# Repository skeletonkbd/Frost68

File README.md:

# Frost68

アクリル積層ケースを使った Alice 配列のキーボードです。（開発時名称: Skeleton68rev2）

Firmware: https://github.com/skeletonkbd/qmk_firmware/tree/Frost68/keyboards/skeletonkbd/frost68

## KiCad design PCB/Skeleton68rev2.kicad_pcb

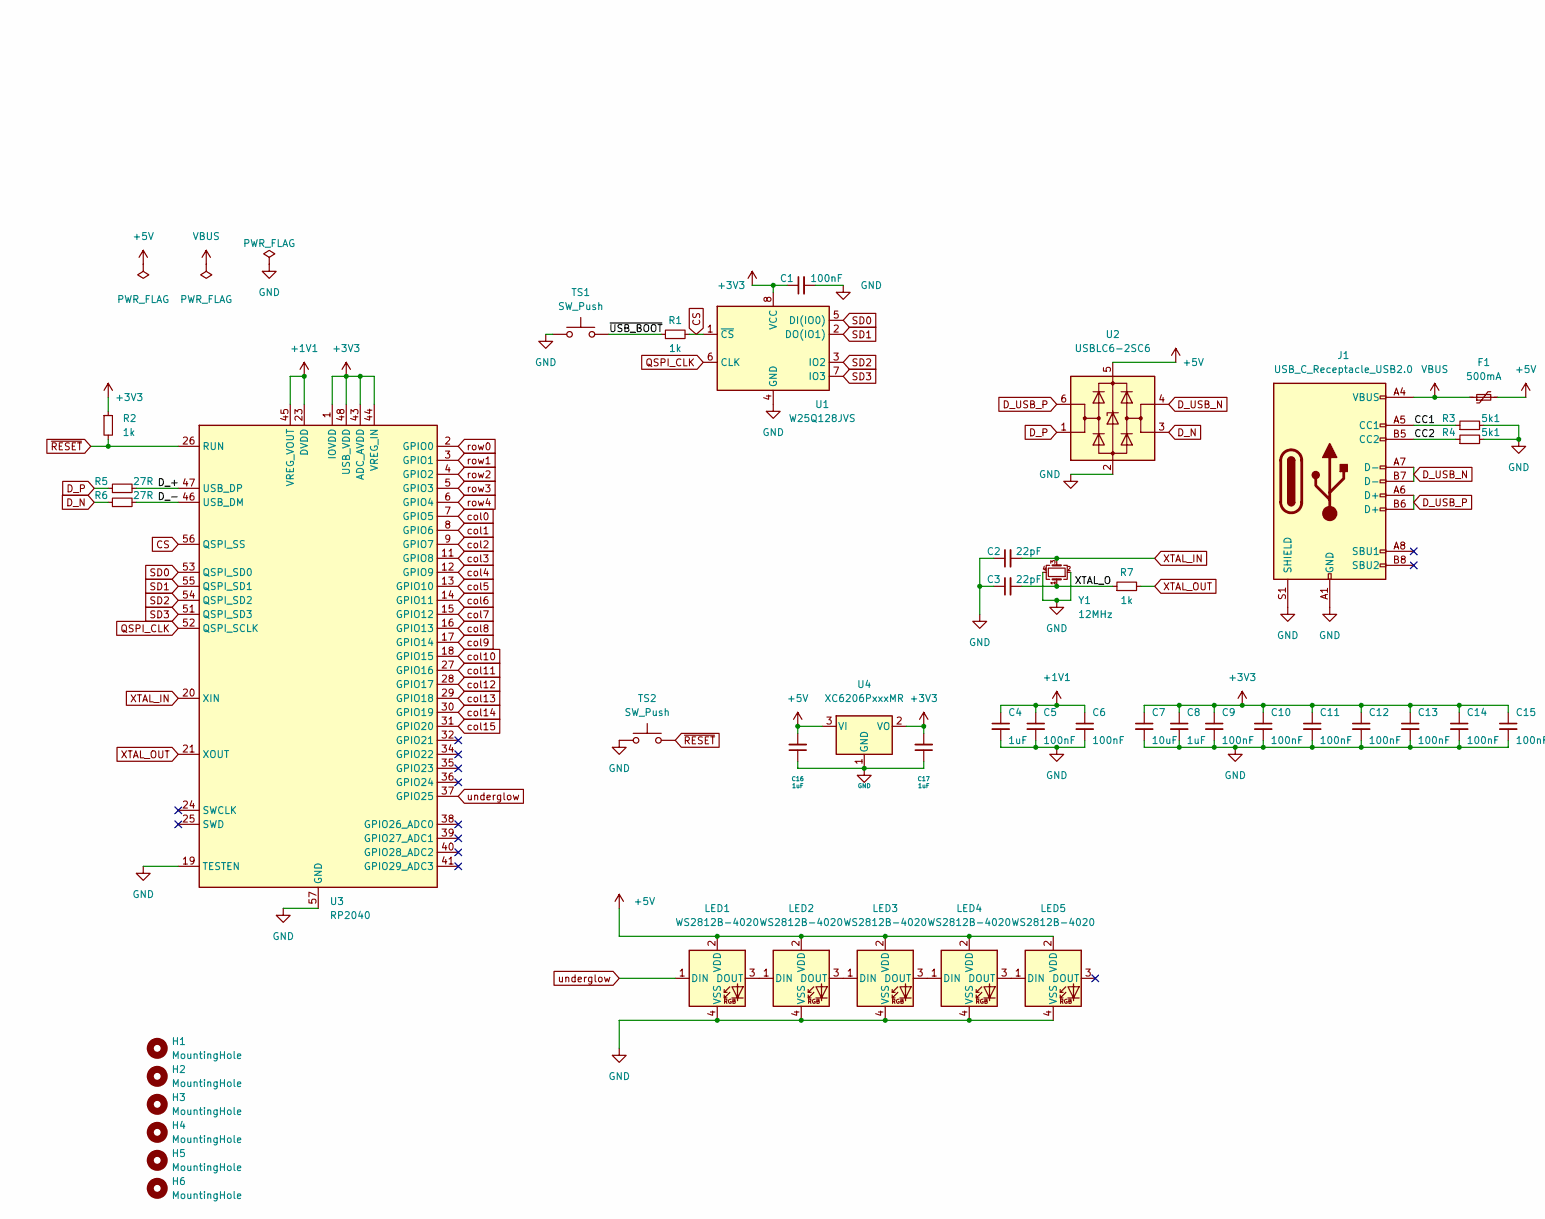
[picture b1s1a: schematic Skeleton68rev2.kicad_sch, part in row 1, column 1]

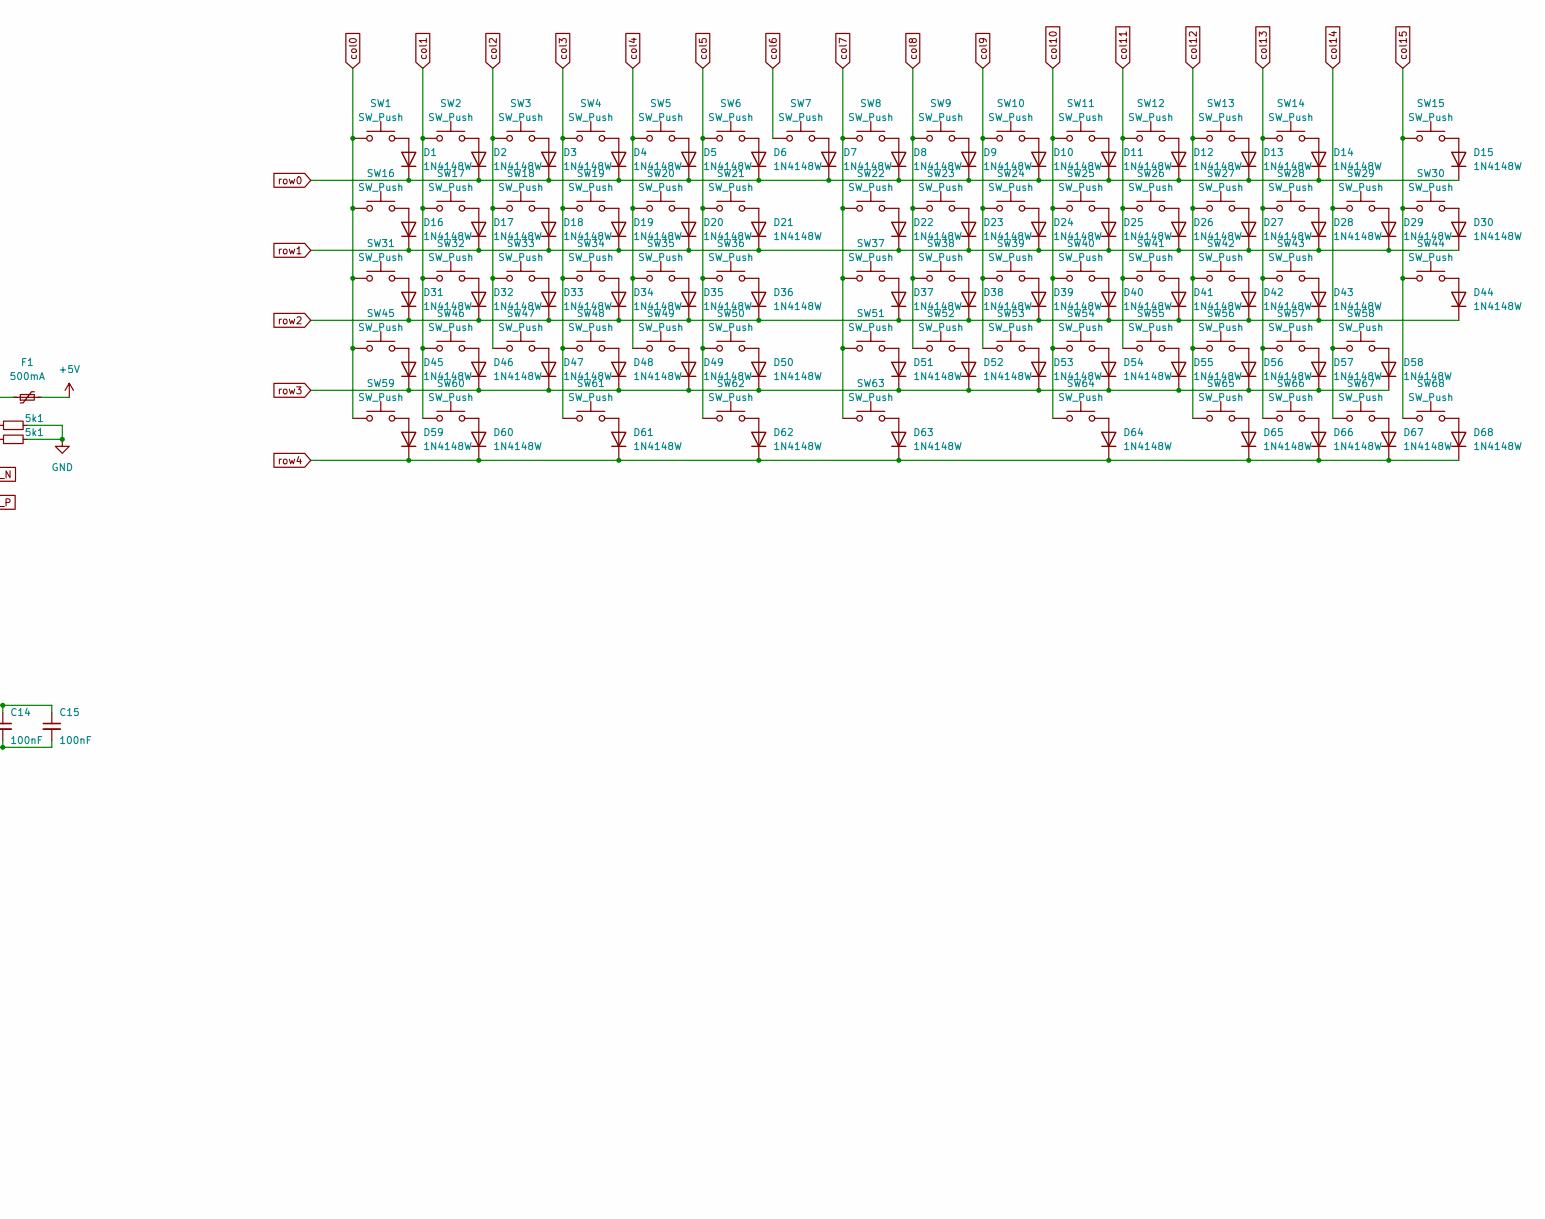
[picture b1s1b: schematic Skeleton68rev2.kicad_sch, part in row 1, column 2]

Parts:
C1, C5, C6, C9, C10, C11, C12, C13, C14, C15: 100nF; C_0402_1005Metric; MPN CL05B104KO5NNNC; LCSC C1525
C2, C3: 22pF; C_0402_1005Metric; MPN 0402CG220J500NT; LCSC C1555
C4, C8, C16, C17: 1uF; C_0402_1005Metric; MPN CL05A105KA5NQNC; LCSC C52923
C7: 10uF; C_0402_1005Metric; MPN CL05A106MQ5NUNC; LCSC C15525
D1, D2, D3, D4, D5, D6, D7, D8, D9, D10, D11, D12, D13, D14, D15, D16, D17, D18, D19, D20, D21, D22, D23, D24, D25, D26, D27, D28, D29, D30, D31, D32, D33, D34, D35, D36, D37, D38, D39, D40, D41, D42, D43, D44, D45, D46, D47, D48, D49, D50, D51, D52, D53, D54, D55, D56, D57, D58, D59, D60, D61, D62, D63, D64, D65, D66, D67, D68: 1N4148W; D_SOD-123
F1: 500mA; Fuse_1206_3216Metric; MPN nSMD050-24V; LCSC C70076
H1, H2, H3, H4, H5, H6: MountingHole; MountingHole_2.2mm_M2
J1: USB_C_Receptacle_USB2.0; USB_C_Receptacle_HRO_TYPE-C-31-M-12; MPN TYPE-C-31-M-12; LCSC C165948
LED1, LED2, LED3, LED4, LED5: WS2812B-4020
R1, R2, R7: 1k; R_0402_1005Metric; MPN 0402WGF1001TCE; LCSC C11702
R3, R4: 5k1; R_0402_1005Metric; MPN 0402WGF5101TCE; LCSC C25905
R5, R6: 27R; R_0603_1608Metric; MPN 0603WAF270JT5E; LCSC C25190
SW1, SW2, SW3, SW4, SW5, SW6, SW7, SW8, SW9, SW10, SW11, SW12, SW13, SW14, SW15, SW16, SW17, SW18, SW19, SW20, SW21, SW22, SW23, SW24, SW25, SW26, SW27, SW28, SW29, SW30, SW31, SW32, SW33, SW34, SW35, SW36, SW37, SW38, SW39, SW40, SW41, SW42, SW43, SW44, SW45, SW46, SW47, SW48, SW49, SW50, SW51, SW52, SW53, SW54, SW55, SW56, SW57, SW58, SW59, SW60, SW61, SW62, SW63, SW64, SW65, SW66, SW67, SW68: SW_Push; MX-Hotswap-1U
TS1, TS2: SW_Push; SW_SPST_SKQG_WithStem; MPN SKQGABE010; LCSC C318884
U1: W25Q128JVS; SOIC-8_5.23x5.23mm_P1.27mm; MPN W25Q16JVSSIQ; LCSC C131025
U2: USBLC6-2SC6; SOT-23-6; MPN USBLC6-2SC6; LCSC C2827654
U3: RP2040; QFN-56-1EP_7x7mm_P0.4mm_EP3.2x3.2mm
U4: XC6206PxxxMR; SOT-23; MPN XC6206P332MR; LCSC C5446
Y1: 12MHz; Crystal_SMD_3225-4Pin_3.2x2.5mm; MPN X322512MSB4SI; LCSC C9002

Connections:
+1V1: C4.1, C5.1, C6.1, U3.23 (DVDD), U3.45 (VREG_VOUT), U3.50 (DVDD)
+3V3: C1.1, C7.1, C8.1, C9.1, C10.1, C11.1, C12.1, C13.1, C14.1, C15.1, C17.2, R2.1, U1.8 (VCC), U3.1 (IOVDD), U3.10 (IOVDD), U3.22 (IOVDD), U3.33 (IOVDD), U3.42 (IOVDD), U3.43 (ADC_AVDD), U3.44 (VREG_IN), U3.48 (USB_VDD), U3.49 (IOVDD), U4.2 (VO)
+5V: C16.2, F1.2, LED1.2 (VDD), LED2.2 (VDD), LED3.2 (VDD), LED4.2 (VDD), LED5.2 (VDD), U2.5 (VBUS), U4.3 (VI)
/CC1: J1.A5 (CC1), R3.1
/CC2: J1.B5 (CC2), R4.1
/D_+: R5.2, U3.47 (USB_DP)
/D_-: R6.2, U3.46 (USB_DM)
/XTAL_O: C3.2, R7.1, Y1.1
/~USB_BOOT: R1.1, TS1.2
CS: R1.2, U1.1 (~CS), U3.56 (QSPI_SS)
D_N: R6.1, U2.3 (I/O2)
D_P: R5.1, U2.1 (I/O1)
D_USB_N: J1.A7 (D-), J1.B7 (D-), U2.4 (I/O2)
D_USB_P: J1.A6 (D+), J1.B6 (D+), U2.6 (I/O1)
GND: C1.2, C2.1, C3.1, C4.2, C5.2, C6.2, C7.2, C8.2, C9.2, C10.2, C11.2, C12.2, C13.2, C14.2, C15.2, C16.1, C17.1, J1.A1 (GND), J1.A12 (GND), J1.B1 (GND), J1.B12 (GND), J1.S1 (SHIELD), LED1.4 (VSS), LED2.4 (VSS), LED3.4 (VSS), LED4.4 (VSS), LED5.4 (VSS), R3.2, R4.2, TS1.1, TS2.1, U1.4 (GND), U2.2 (GND), U3.19 (TESTEN), U3.57 (GND), U4.1 (GND), Y1.2, Y1.4
unnamed: D1.2 (A), SW1.2
unnamed: D2.2 (A), SW2.2
unnamed: D3.2 (A), SW3.2
unnamed: D4.2 (A), SW4.2
unnamed: D5.2 (A), SW5.2
unnamed: D6.2 (A), SW6.2
unnamed: D7.2 (A), SW7.2
unnamed: D8.2 (A), SW8.2
unnamed: D9.2 (A), SW9.2
unnamed: D10.2 (A), SW10.2
unnamed: D11.2 (A), SW11.2
unnamed: D12.2 (A), SW12.2
unnamed: D13.2 (A), SW13.2
unnamed: D14.2 (A), SW14.2
unnamed: D15.2 (A), SW15.2
unnamed: D16.2 (A), SW16.2
unnamed: D17.2 (A), SW17.2
unnamed: D18.2 (A), SW18.2
unnamed: D19.2 (A), SW19.2
unnamed: D20.2 (A), SW20.2
unnamed: D21.2 (A), SW21.2
unnamed: D22.2 (A), SW22.2
unnamed: D23.2 (A), SW23.2
unnamed: D24.2 (A), SW24.2
unnamed: D25.2 (A), SW25.2
unnamed: D26.2 (A), SW26.2
unnamed: D27.2 (A), SW27.2
unnamed: D28.2 (A), SW28.2
unnamed: D29.2 (A), SW29.2
unnamed: D30.2 (A), SW30.2
unnamed: D31.2 (A), SW31.2
unnamed: D32.2 (A), SW32.2
unnamed: D33.2 (A), SW33.2
unnamed: D34.2 (A), SW34.2
unnamed: D35.2 (A), SW35.2
unnamed: D36.2 (A), SW36.2
unnamed: D37.2 (A), SW37.2
unnamed: D38.2 (A), SW38.2
unnamed: D39.2 (A), SW39.2
unnamed: D40.2 (A), SW40.2
unnamed: D41.2 (A), SW41.2
unnamed: D42.2 (A), SW42.2
unnamed: D43.2 (A), SW43.2
unnamed: D44.2 (A), SW44.2
unnamed: D45.2 (A), SW45.2
unnamed: D46.2 (A), SW46.2
unnamed: D47.2 (A), SW47.2
unnamed: D48.2 (A), SW48.2
unnamed: D49.2 (A), SW49.2
unnamed: D50.2 (A), SW50.2
unnamed: D51.2 (A), SW51.2
unnamed: D52.2 (A), SW52.2
unnamed: D53.2 (A), SW53.2
unnamed: D54.2 (A), SW54.2
unnamed: D55.2 (A), SW55.2
unnamed: D56.2 (A), SW56.2
unnamed: D57.2 (A), SW57.2
unnamed: D58.2 (A), SW58.2
unnamed: D59.2 (A), SW59.2
unnamed: D60.2 (A), SW60.2
unnamed: D61.2 (A), SW61.2
unnamed: D62.2 (A), SW62.2
unnamed: D63.2 (A), SW63.2
unnamed: D64.2 (A), SW64.2
unnamed: D65.2 (A), SW65.2
unnamed: D66.2 (A), SW66.2
unnamed: D67.2 (A), SW67.2
unnamed: D68.2 (A), SW68.2
unnamed: LED1.3 (DOUT), LED2.1 (DIN)
unnamed: LED2.3 (DOUT), LED3.1 (DIN)
unnamed: LED3.3 (DOUT), LED4.1 (DIN)
unnamed: LED4.3 (DOUT), LED5.1 (DIN)
QSPI_CLK: U1.6 (CLK), U3.52 (QSPI_SCLK)
SD0: U1.5 (DI(IO0)), U3.53 (QSPI_SD0)
SD1: U1.2 (DO(IO1)), U3.55 (QSPI_SD1)
SD2: U1.3 (IO2), U3.54 (QSPI_SD2)
SD3: U1.7 (IO3), U3.51 (QSPI_SD3)
VBUS: F1.1, J1.A4 (VBUS), J1.A9 (VBUS), J1.B4 (VBUS), J1.B9 (VBUS)
XTAL_IN: C2.2, U3.20 (XIN), Y1.3
XTAL_OUT: R7.2, U3.21 (XOUT)
col0: SW1.1, SW16.1, SW31.1, SW45.1, SW59.1, U3.7 (GPIO5)
col1: SW2.1, SW17.1, SW32.1, SW46.1, SW60.1, U3.8 (GPIO6)
col2: SW3.1, SW18.1, SW33.1, SW47.1, U3.9 (GPIO7)
col3: SW4.1, SW19.1, SW34.1, SW48.1, SW61.1, U3.11 (GPIO8)
col4: SW5.1, SW20.1, SW35.1, SW49.1, U3.12 (GPIO9)
col5: SW6.1, SW21.1, SW36.1, SW50.1, SW62.1, U3.13 (GPIO10)
col6: SW7.1, U3.14 (GPIO11)
col7: SW8.1, SW22.1, SW37.1, SW51.1, SW63.1, U3.15 (GPIO12)
col8: SW9.1, SW23.1, SW38.1, SW52.1, U3.16 (GPIO13)
col9: SW10.1, SW24.1, SW39.1, SW53.1, U3.17 (GPIO14)
col10: SW11.1, SW25.1, SW40.1, SW54.1, SW64.1, U3.18 (GPIO15)
col11: SW12.1, SW26.1, SW41.1, SW55.1, U3.27 (GPIO16)
col12: SW13.1, SW27.1, SW42.1, SW56.1, SW65.1, U3.28 (GPIO17)
col13: SW14.1, SW28.1, SW43.1, SW57.1, SW66.1, U3.29 (GPIO18)
col14: SW29.1, SW58.1, SW67.1, U3.30 (GPIO19)
col15: SW15.1, SW30.1, SW44.1, SW68.1, U3.31 (GPIO20)
row0: D1.1 (K), D2.1 (K), D3.1 (K), D4.1 (K), D5.1 (K), D6.1 (K), D7.1 (K), D8.1 (K), D9.1 (K), D10.1 (K), D11.1 (K), D12.1 (K), D13.1 (K), D14.1 (K), D15.1 (K), U3.2 (GPIO0)
row1: D16.1 (K), D17.1 (K), D18.1 (K), D19.1 (K), D20.1 (K), D21.1 (K), D22.1 (K), D23.1 (K), D24.1 (K), D25.1 (K), D26.1 (K), D27.1 (K), D28.1 (K), D29.1 (K), D30.1 (K), U3.3 (GPIO1)
row2: D31.1 (K), D32.1 (K), D33.1 (K), D34.1 (K), D35.1 (K), D36.1 (K), D37.1 (K), D38.1 (K), D39.1 (K), D40.1 (K), D41.1 (K), D42.1 (K), D43.1 (K), D44.1 (K), U3.4 (GPIO2)
row3: D45.1 (K), D46.1 (K), D47.1 (K), D48.1 (K), D49.1 (K), D50.1 (K), D51.1 (K), D52.1 (K), D53.1 (K), D54.1 (K), D55.1 (K), D56.1 (K), D57.1 (K), D58.1 (K), U3.5 (GPIO3)
row4: D59.1 (K), D60.1 (K), D61.1 (K), D62.1 (K), D63.1 (K), D64.1 (K), D65.1 (K), D66.1 (K), D67.1 (K), D68.1 (K), U3.6 (GPIO4)
underglow: LED1.1 (DIN), U3.37 (GPIO25)
~RESET: R2.2, TS2.2, U3.26 (RUN)

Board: 2 copper layers, 180 parts (1 on the bottom side), 118 nets, no tracks yet.

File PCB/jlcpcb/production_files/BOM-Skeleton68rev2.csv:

Comment,Designator,Footprint,LCSC
1k,"R1,R2,R7",R_0402_1005Metric,C11702
W25Q128JVS,U1,SOIC-8_5.23x5.23mm_P1.27mm,C131025
100nF,"C1,C10,C11,C12,C13,C14,C15,C5,C6,C9",C_0402_1005Metric,C1525
10uF,C7,C_0402_1005Metric,C15525
22pF,"C2,C3",C_0402_1005Metric,C1555
USB_C_Receptacle_USB2.0,J1,USB_C_Receptacle_HRO_TYPE-C-31-M-12,C165948
RP2040,U3,QFN-56-1EP_7x7mm_P0.4mm_EP3.2x3.2mm,C2040
27R,"R5,R6",R_0603_1608Metric,C25190
5k1,"R3,R4",R_0402_1005Metric,C25905
SW_Push,"SW1,SW10,SW11,SW12,SW13,SW14,SW15,SW16,SW17,SW18,SW19,SW2,SW20,SW21,SW22,SW23,SW24,SW25,SW26,SW27,SW28,SW29,SW3,SW30,SW31,SW32,SW33,SW34,SW35,SW36,SW37,SW38,SW39,SW4,SW40,SW41,SW42,SW43,SW44,SW45,SW46,SW47,SW48,SW49,SW5,SW50,SW51,SW52,SW53,SW54,SW55,SW56,SW57,SW58,SW59,SW6,SW60,SW61,SW62,SW63,SW64,SW65,SW66,SW67,SW68,SW7,SW8,SW9",MX-Hotswap-1U,C2803348
USBLC6-2SC6,U2,SOT-23-6,C2827654
1uF,"C16,C17,C4,C8",C_0402_1005Metric,C52923
XC6206PxxxMR,U4,SOT-23,C5446
500mA,F1,Fuse_1206_3216Metric,C70076
1N4148W,"D1,D10,D11,D12,D13,D14,D15,D16,D17,D18,D19,D2,D20,D21,D22,D23,D24,D25,D26,D27,D28,D29,D3,D30,D31,D32,D33,D34,D35,D36,D37,D38,D39,D4,D40,D41,D42,D43,D44,D45,D46,D47,D48,D49,D5,D50,D51,D52,D53,D54,D55,D56,D57,D58,D59,D6,D60,D61,D62,D63,D64,D65,D66,D67,D68,D7,D8,D9",D_SOD-123,C81598
12MHz,Y1,Crystal_SMD_3225-4Pin_3.2x2.5mm,C9002
WS2812B-4020,"LED1,LED10,LED11,LED12,LED13,LED14,LED15,LED16,LED17,LED18,LED19,LED2,LED20,LED21,LED22,LED23,LED24,LED25,LED26,LED27,LED28,LED29,LED3,LED30,LED31,LED4,LED5,LED6,LED7,LED8,LED9",WS2812B-4020,C965557
Fiducial,FID4,Fiducial_1mm_Mask2mm,
Fiducial,FID3,Fiducial_1mm_Mask2mm,
Fiducial,FID2,Fiducial_1mm_Mask2mm,
Fiducial,FID1,Fiducial_1mm_Mask2mm,
MountingHole,H6,MountingHole_2.2mm_M2,
MountingHole,H4,MountingHole_2.2mm_M2,
MountingHole,H1,MountingHole_2.2mm_M2,
MountingHole,H3,MountingHole_2.2mm_M2,
MountingHole,H5,MountingHole_2.2mm_M2,
MountingHole,H2,MountingHole_2.2mm_M2,
MountingHole,H7,MountingHole_2.2mm_M2,
MountingHole,H8,MountingHole_2.2mm_M2,

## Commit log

2022-11-24 回路図作成
2022-11-25 ライセンス変更
2022-11-25 Update LICENSE
2022-12-18 side mounted LEDs
2023-01-05 v1.0
2023-02-06 Add Plate
2023-06-13 extend sk6812mini-e holes

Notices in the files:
README.md:
License: CC BY-NC 4.0
